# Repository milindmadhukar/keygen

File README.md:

# Keygen

**A wireless split ergonomic keyboard with a custom two-layer PCB designed in KiCad 10.**

Keygen is a one-off build: 66 keys over two column-staggered halves, a 2 × 2 thumb cluster, a rotary
encoder and a 0.96-inch OLED on each half, and per-key RGB lighting. Each half has its own
nRF52840 controller hidden on the PCB underside, and an optional printed wedge tents it 13°. The keyboard reaches the host over Bluetooth or
USB-C, and the halves talk to each other over Bluetooth.

The schematic, placement and most of the routing are generated by the Python scripts in
[`tools/`](tools/), and so are the switch plate and the 3D-printed case.
[`tools/regen.py`](tools/regen.py) keeps every generated file current with its sources. The name and the
silkscreen artwork come from Martin Garrix's track *Keygen* (STMPD RCRDS); see
[Silkscreen artwork](notes/16%20-%20hardware%20reference.md#silkscreen-artwork).
[`tools/check_mechanical.py`](tools/check_mechanical.py) checks the plate, case and component
clearances, including the battery stack at full gasket travel.

**To build one, follow [INSTRUCTIONS.md](INSTRUCTIONS.md).**

## Specifications

| | |
|---|---|
| Layout | Column-staggered QWERTY, six columns per hand plus an extra bottom row |
| Keys | 66 (33 per half): 52 × 1u, 14 × 1.25u |
| Thumb cluster | 2 × 2 block rotated 30° (two 1u over two 1.25u) plus one 1.25u key per hand |
| Encoders | HongYan EC11H with a 20 mm D shaft on each half, fixed to the top frame and plugged into a pin header on the PCB, with a 17 mm aluminium D-shaft knob, in the key matrix. Left: scroll wheel, press for middle click. Right: volume, press to mute |
| Displays | 0.96 in. 128 × 64 SSD1306 OLED per half (I2C), held in the top frame and plugged into the PCB, showing ZMK's status screen |
| Switches | Akko V3 Lavender Purple Pro (tactile, 5-pin) in Kailh hotswap sockets (CPG151101S11) |
| Keycaps | Blank DSA PBT, smoke translucent |
| Lighting | 33 SK6812MINI-E reverse-mount RGB backlights per half, on a 5 V rail from a TPS61023 boost that the firmware switches off with the lighting. An SN74LV1T125 buffer drives their data at 5 V. ZMK's addressable RGB driver; on battery the lighting is optional (a System-layer key), dimmer, and off on a low cell |
| Controller | nRF52840 SuperMini (nice!nano v2 clone, Pro Micro format), one per half, socketed on the underside |
| Connectivity | Host: USB-C (left half) or Bluetooth, 5 profiles. Halves: Bluetooth split |
| Power | KP-355085 LiPo pouch per half (3.5 × 50 × 85 mm, listed 3000 mAh) with a protection board, JST-PH connector, slide switch driving a P-MOSFET battery switch. Each half charges from its own USB-C at about 300 mA |
| PCB | 2 layers, FR-4 1.6 mm, 1 oz copper, HASL, black soldermask with white silkscreen. One half is 160.2 × 126.0 mm |
| Switch plate | Clear polycarbonate 1.5 mm, CNC-routed, with eight gasket tabs per half |
| Case | 3D-printed PETG, gasket-mounted: a bottom shell and a top frame per half, 175.4 × 143.7 × 24.5 mm. The top frame covers the plate round the keycaps and the knob, and holds the OLED and the encoder. Rubber feet, and a steel disc set flush into each floor |
| Tenting | Optional 3D-printed 13° PETG wedge per half, held by four N35 10 × 3 mm magnets to the steel disc, with the feet standing in recesses in its top face |
| Foam | Poron ring switch pads (0.5 mm) on the PCB, EVA plate foam (2 mm) taped under the plate, EVA case foam (5 mm) on the case floor |
| Firmware | [ZMK](https://zmk.dev) `main` (Zephyr 4.1): QWERTY base with Nav, Fn and System layers, ZMK Studio |

## Gallery

The lit pictures are Cycles renders of the [Blender scene](notes/17%20-%20building%20from%20source.md#blender-scene),
which is rebuilt from the board and the case on request; the case layers and the PCB come from KiCad.

<details>
<summary>More renders and animations</summary>

**Both OLEDs booting.** A closeup of both screens playing the firmware boot sequence.

**Per-key lighting.** The SK6812MINI-E LEDs shine up through the switches' clear tops and the smoke
translucent caps. The [logic audit](docs/logic-audit.md) records the current and voltage limits that
still need a powered prototype test before brightness or battery life can be promised.

**All round.**

**From above.** The top frame's deck round the keycaps, the OLED window and the knob.

**From the side.** The back edge of each half, with its USB-C port and power switch.

**Underneath.** The bottom shells, with the counterbored case screws and the reset pinhole.

**Tenting.** Each half on its wedge, and the wedges' top faces: four recesses for the rubber feet, and
four pockets for the magnets under the steel disc.

**Knob and thumb cluster.**

**Status screen.** ZMK's status screen on the left OLED: Bluetooth profile, battery and layer. The
Keygen screens, with their boot animation and lighting menu, are in
[`firmware/README.md`](firmware/README.md#oled-screens).

**Case layers.** Bottom shell, case foam, standoff screws, PCB, switch pads, shims and standoffs,
plate foam, gasket strips under and over the plate tabs, plate and top frame.

**Bare PCB.** Black soldermask with white silkscreen artwork on both sides; see
[Silkscreen artwork](notes/16%20-%20hardware%20reference.md#silkscreen-artwork).

**PCB underside, assembled.** The controllers, power switches, battery connectors and reset buttons
sit on the back.

Renders of the case parts, the plate and the routing are in the [`media` release](https://github.com/milindmadhukar/keygen/releases/tag/media).

</details>

## Documentation

| Document | What it covers |
|---|---|
| [Build guide](INSTRUCTIONS.md) | Parts list, what to order and when, what goes on which side, one section per part with close-ups, flashing, closing the case, troubleshooting |
| [Hardware reference](notes/16%20-%20hardware%20reference.md) | Electronics, PCB rules, plate, case, foam and the silkscreen artwork |
| [Building from source](notes/17%20-%20building%20from%20source.md) | Requirements, the schematic and PCB pipeline, the plate and case, the [Blender scene](notes/17%20-%20building%20from%20source.md#blender-scene), every generated file |
| [Firmware](firmware/README.md) | ZMK configuration: keymap, OLED screens, hardware support, building and flashing |
| [Design notes](notes/index.md) | The Obsidian design notes: layout, controller, PCB, case, final design, datasheet audit |
| [Encoder mount](docs/encoder-mount.md) | The encoder boss, knob clearance, the plate and PCB openings, the cable and a printable test coupon |
| [Build plan](plan/index.html) | Layout drawing, connectivity, parts, pin budget and checklist. Open it in a browser |
| [Printed reference (PDF)](https://github.com/milindmadhukar/keygen/releases/download/build/keygen-reference.pdf) | A4, black and white: each half's key layout with every layer's legends, the case footprint and the back of the board at 1:1, the power parts and each part type close up, the keymap, the key matrix with the controller's pads, and the parts lists |
| [Schematic (PDF)](https://github.com/milindmadhukar/keygen/releases/download/build/keygen-schematic.pdf) | A top sheet with left (refs 1xx) and right (refs 2xx) sub-sheets |
| [KiCad project](pcb/keygen.kicad_pro) | Schematic and PCB, KiCad 10. Both halves are in one board file as two separate outlines |
| [Build files](https://github.com/milindmadhukar/keygen/releases/tag/build) | The PCB and plate Gerbers, case and wedge STLs and STEPs, foam cut files and plate print PDFs, as a release |
| [Ordering notes](fab/ORDER.md) | PCB order-form settings and what to check in the DFM report |
| [Plate ordering notes](case/plate/PLATE.md) | The DXFs for routing the switch plates from polycarbonate sheet, and the Gerbers for an FR-4 plate from a PCB fab |
| [Assembly BOM](fab/BOM.md) | Every part's references per half, with quantities and soldering notes |
| [Parts and sources](plan/bom.html) | Shopping list with Indian and import sources (from [`bom/bom.csv`](bom/bom.csv)) |
| [Shopping checklist](bom/CHECKLIST.md) | What to buy, from which store, with links and prices, to tick off |
| [Datasheets](docs/datasheets/README.md) | Every part's datasheet, with the page each design fact comes from |

## Firmware

Keygen runs [ZMK](https://zmk.dev), one build per half on the nice!nano v2 target, with the left half as
the central. The configuration builds; it has not yet run on the boards. GitHub Actions builds the
UF2s on every push that changes `firmware/`. The keymap, the build and the flashing steps are in
[`firmware/README.md`](firmware/README.md).

## Repository layout

```
keygen/
├── INSTRUCTIONS.md Build guide
├── pcb/            KiCad 10 project: schematic (generated), PCB, plate, project footprints and 3D models
├── tools/          Python scripts that generate, route, check and export the design
├── fab/            Assembly BOMs and ordering notes (the Gerbers are in the build release)
├── case/           Plate ordering notes (the case, wedge, plate and foam files are in the build release)
├── bom/            Bill of materials with sources (bom.csv) and the shopping checklist
├── plan/           Build plan and parts list as HTML
├── docs/           Datasheet index (the PDFs are in the datasheets release)
├── assets/         Keymap pictures and assembly figures (the renders are in the media release)
├── blender/        Blender studio scene with the materials and the lit LEDs; it links the generated parts
├── notes/          Design notes, hardware reference and build pipeline (Obsidian Markdown)
├── firmware/       ZMK configuration: shield, keymap, builds
└── lib/            Git submodules: marbastlib and Keebio-Parts footprint libraries, KeyV2 keycaps
```

## Project status

- [x] Layout and schematic, ERC clean
- [x] PCB placed, routed, DRC clean with schematic parity
- [x] Datasheet audit with no failures
- [x] Manufacturing files and assembly BOM
- [x] Parts sourced and priced
- [ ] Boards ordered and assembled
- [x] ZMK firmware builds
- [ ] ZMK firmware tested on the boards
- [x] Switch plate, gasket-mounted case and tenting wedges designed, fit-checked against the PCB
- [ ] Case and wedges printed

## Credits and licenses

- Footprints from [marbastlib](https://github.com/ebastler/marbastlib) (CERN-OHL-P v2) and
  [Keebio-Parts](https://github.com/keebio/Keebio-Parts.pretty) (MIT), included as git submodules.
- DSA keycap models generated with [KeyV2](https://github.com/rsheldiii/KeyV2) (GPL-3.0), a git submodule.
- MX switch 3D model from [kiswitch](https://github.com/kiswitch/kiswitch) (MIT / CC-BY-SA 4.0); see
  [`pcb/lib/keygen.3dshapes/NOTICE.md`](pcb/lib/keygen.3dshapes/NOTICE.md).
- Datasheets in the [`datasheets` release](https://github.com/milindmadhukar/keygen/releases/tag/datasheets) belong to their manufacturers.

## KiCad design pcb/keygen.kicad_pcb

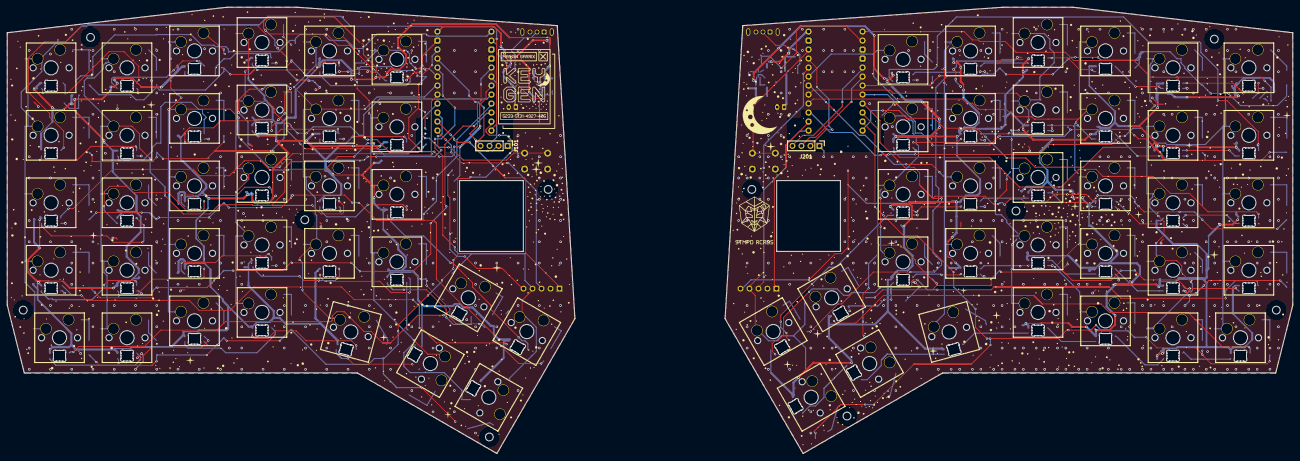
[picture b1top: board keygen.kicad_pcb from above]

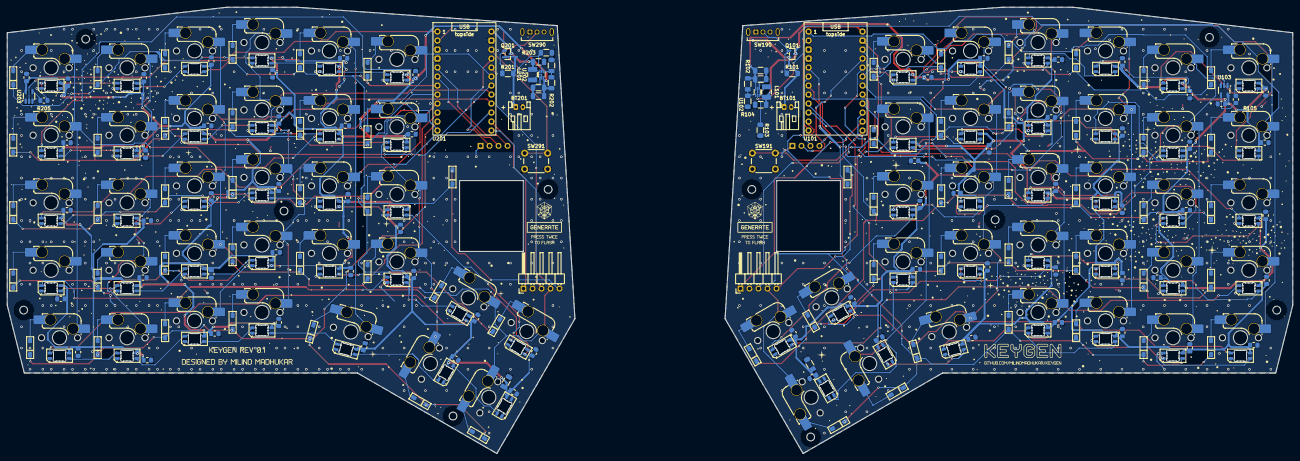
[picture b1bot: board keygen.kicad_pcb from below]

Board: 2 copper layers, 362.9 x 126.0 mm, 318 parts (304 on the bottom side), 190 nets.

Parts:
BT101, BT201: LiPo 3.7V 3000mAh; JST_PH_S2B-PH-K_1x02_P2.00mm_Horizontal
C101, C104, C201, C204: 22uF; C_1206_3216Metric_Pad1.33x1.80mm_HandSolder
C102, C111, C112, C113, C114, C115, C116, C117, C118, C119, C120, C121, C122, C123, C124, C125, C126, C127, C128, C129, C130, C131, C132, C133, C134, C135, C136, C137, C138, C139, C140, C141, C142, C143, C202, C211, C212, C213, C214, C215, C216, C217, C218, C219, C220, C221, C222, C223, C224, C225, C226, C227, C228, C229, C230, C231, C232, C233, C234, C235, C236, C237, C238, C239, C240, C241, C242, C243: 100nF; C_0805_2012Metric_Pad1.18x1.45mm_HandSolder
C103, C105, C203, C205: 10uF; C_1206_3216Metric_Pad1.33x1.80mm_HandSolder
D101, D102, D103, D104, D105, D106, D107, D108, D109, D110, D111, D112, D113, D114, D115, D116, D117, D118, D119, D120, D121, D122, D123, D124, D125, D126, D127, D128, D129, D130, D131, D132, D133, D134, D201, D202, D203, D204, D205, D206, D207, D208, D209, D210, D211, D212, D213, D214, D215, D216, D217, D218, D219, D220, D221, D222, D223, D224, D225, D226, D227, D228, D229, D230, D231, D232, D233, D234: 1N4148W; D_SOD-123_HandSolder
ENC101, ENC201: EC11; EC11_Case_Mount
H101, H102, H103, H104, H105, H201, H202, H203, H204, H205: M2; MountingHole_2.2mm_M2
J101, J201: OLED 0.96in I2C; PinHeader_1x04_P2.54mm_Vertical
J102, J202: Encoder lead, 1x5 right angle; PinHeader_1x05_P2.54mm_Horizontal
L101, L201: 1uH; L_1210_3225Metric_Pad1.42x2.65mm_HandSolder
LED101, LED102, LED103, LED104, LED105, LED106, LED107, LED108, LED109, LED110, LED111, LED112, LED113, LED114, LED115, LED116, LED117, LED118, LED119, LED120, LED121, LED122, LED123, LED124, LED125, LED126, LED127, LED128, LED129, LED130, LED131, LED132, LED133, LED201, LED202, LED203, LED204, LED205, LED206, LED207, LED208, LED209, LED210, LED211, LED212, LED213, LED214, LED215, LED216, LED217, LED218, LED219, LED220, LED221, LED222, LED223, LED224, LED225, LED226, LED227, LED228, LED229, LED230, LED231, LED232, LED233: SK6812MINI-E; LED_SK6812MINI-E_3.2x2.8mm_P1.5mm_ReverseMount
Q101, Q201: AO3401A; SOT-23
R101, R201: 1M; R_1206_3216Metric_Pad1.30x1.75mm_HandSolder
R102, R202: 732k; R_1206_3216Metric_Pad1.30x1.75mm_HandSolder
R103, R104, R203, R204: 100k; R_1206_3216Metric_Pad1.30x1.75mm_HandSolder
R105, R205: 330; R_0805_2012Metric_Pad1.20x1.40mm_HandSolder
SW101: =; SW_MX_HS_CPG151101S11_1.25u
SW102: 1; SW_MX_HS_CPG151101S11_1u
SW103: 2; SW_MX_HS_CPG151101S11_1u
SW104: 3; SW_MX_HS_CPG151101S11_1u
SW105: 4; SW_MX_HS_CPG151101S11_1u
SW106: 5; SW_MX_HS_CPG151101S11_1u
SW108: Tab; SW_MX_HS_CPG151101S11_1.25u
SW109: Q; SW_MX_HS_CPG151101S11_1u
SW110: W; SW_MX_HS_CPG151101S11_1u
SW111: E; SW_MX_HS_CPG151101S11_1u
SW112: R; SW_MX_HS_CPG151101S11_1u
SW113: T; SW_MX_HS_CPG151101S11_1u
SW114: Esc; SW_MX_HS_CPG151101S11_1.25u
SW115: A; SW_MX_HS_CPG151101S11_1u
SW116: S; SW_MX_HS_CPG151101S11_1u
SW117: D; SW_MX_HS_CPG151101S11_1u
SW118: F; SW_MX_HS_CPG151101S11_1u
SW119: G; SW_MX_HS_CPG151101S11_1u
SW120, SW220: Alt; SW_MX_HS_CPG151101S11_1u
SW121, SW221: Shift; SW_MX_HS_CPG151101S11_1.25u
SW122: Z; SW_MX_HS_CPG151101S11_1u
SW123: X; SW_MX_HS_CPG151101S11_1u
SW124: C; SW_MX_HS_CPG151101S11_1u
SW125: V; SW_MX_HS_CPG151101S11_1u
SW126: B; SW_MX_HS_CPG151101S11_1u
SW127, SW227: Ctrl; SW_MX_HS_CPG151101S11_1u
SW128: `; SW_MX_HS_CPG151101S11_1u
SW129: Caps; SW_MX_HS_CPG151101S11_1u
SW130: Left; SW_MX_HS_CPG151101S11_1u
SW131: Right; SW_MX_HS_CPG151101S11_1u
SW132: Super; SW_MX_HS_CPG151101S11_1.25u
SW133: Bksp; SW_MX_HS_CPG151101S11_1.25u
SW134: Del; SW_MX_HS_CPG151101S11_1.25u
SW190, SW290: SK12D07VG5 power; SW_SK12D07VG5
SW191, SW291: Reset; SW_PUSH_6mm_H5mm
SW201: -; SW_MX_HS_CPG151101S11_1.25u
SW202: 0; SW_MX_HS_CPG151101S11_1u
SW203: 9; SW_MX_HS_CPG151101S11_1u
SW204: 8; SW_MX_HS_CPG151101S11_1u
SW205: 7; SW_MX_HS_CPG151101S11_1u
SW206: 6; SW_MX_HS_CPG151101S11_1u
SW208: \; SW_MX_HS_CPG151101S11_1.25u
SW209: P; SW_MX_HS_CPG151101S11_1u
SW210: O; SW_MX_HS_CPG151101S11_1u
SW211: I; SW_MX_HS_CPG151101S11_1u
SW212: U; SW_MX_HS_CPG151101S11_1u
SW213: Y; SW_MX_HS_CPG151101S11_1u
SW214: '; SW_MX_HS_CPG151101S11_1.25u
SW215: ;; SW_MX_HS_CPG151101S11_1u
SW216: L; SW_MX_HS_CPG151101S11_1u
SW217: K; SW_MX_HS_CPG151101S11_1u
SW218: J; SW_MX_HS_CPG151101S11_1u
SW219: H; SW_MX_HS_CPG151101S11_1u
SW222: /; SW_MX_HS_CPG151101S11_1u
SW223: .; SW_MX_HS_CPG151101S11_1u
SW224: ,; SW_MX_HS_CPG151101S11_1u
SW225: M; SW_MX_HS_CPG151101S11_1u
SW226: N; SW_MX_HS_CPG151101S11_1u
SW228: ]; SW_MX_HS_CPG151101S11_1u
SW229: [; SW_MX_HS_CPG151101S11_1u
SW230: Down; SW_MX_HS_CPG151101S11_1u
SW231: Up; SW_MX_HS_CPG151101S11_1u
SW232: Fn; SW_MX_HS_CPG151101S11_1.25u
SW233: Space; SW_MX_HS_CPG151101S11_1.25u
SW234: Enter; SW_MX_HS_CPG151101S11_1.25u
U101, U201: nRF52840 Pro Micro; nice_nano_H_USBup
U102, U202: TPS61023; SOT-563_HandSolder
U103, U203: SN74LV1T125; SOT-23-5_HandSoldering

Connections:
/left/BAT_GATE: Q101.1, R101.1, SW190.2
/left/BAT_RAW: BT101.1, Q101.2, R101.2
/left/COL0: SW101.1, SW108.1, SW114.1, SW121.1, SW128.1, U101.12
/left/COL1: SW102.1, SW109.1, SW115.1, SW122.1, SW129.1, U101.22
/left/COL2: SW103.1, SW110.1, SW116.1, SW123.1, SW130.1, U101.21
/left/COL3: SW104.1, SW111.1, SW117.1, SW124.1, SW131.1, U101.20
/left/COL4: SW105.1, SW112.1, SW118.1, SW125.1, SW132.1, U101.19
/left/COL5: SW106.1, SW113.1, SW119.1, SW126.1, SW133.1, U101.18
/left/COL6: J102.4, SW120.1, SW127.1, SW134.1, U101.17
/left/ENC_A: J102.1, U101.23
/left/ENC_B: J102.3, U101.24
/left/GND: BT101.2, C101.2, C102.2, C103.2, C104.2, C105.2, C111.2, C112.2, C113.2, C114.2, C115.2, C116.2, C117.2, C118.2, C119.2, C120.2, C121.2, C122.2, C123.2, C124.2, C125.2, C126.2, C127.2, C128.2, C129.2, C130.2, C131.2, C132.2, C133.2, C134.2, C135.2, C136.2, C137.2, C138.2, C139.2, C140.2, C141.2, C142.2, C143.2, J101.1, J102.2, LED101.1, LED102.1, LED103.1, LED104.1, LED105.1, LED106.1, LED107.1, LED108.1, LED109.1, LED110.1, LED111.1, LED112.1, LED113.1, LED114.1, LED115.1, LED116.1, LED117.1, LED118.1, LED119.1, LED120.1, LED121.1, LED122.1, LED123.1, LED124.1, LED125.1, LED126.1, LED127.1, LED128.1, LED129.1, LED130.1, LED131.1, LED132.1, LED133.1, R103.2, R104.2, SW190.1, SW191.2, U101.3, U101.4, U101.14, U102.4, U103.1, U103.3
/left/K00: D101.2, SW101.2
/left/K01: D102.2, SW102.2
/left/K02: D103.2, SW103.2
/left/K03: D104.2, SW104.2
/left/K04: D105.2, SW105.2
/left/K05: D106.2, SW106.2
/left/K06: D107.2, J102.5
/left/K10: D108.2, SW108.2
/left/K11: D109.2, SW109.2
/left/K12: D110.2, SW110.2
/left/K13: D111.2, SW111.2
/left/K14: D112.2, SW112.2
/left/K15: D113.2, SW113.2
/left/K20: D114.2, SW114.2
/left/K21: D115.2, SW115.2
/left/K22: D116.2, SW116.2
/left/K23: D117.2, SW117.2
/left/K24: D118.2, SW118.2
/left/K25: D119.2, SW119.2
/left/K26: D120.2, SW120.2
/left/K30: D121.2, SW121.2
/left/K31: D122.2, SW122.2
/left/K32: D123.2, SW123.2
/left/K33: D124.2, SW124.2
/left/K34: D125.2, SW125.2
/left/K35: D126.2, SW126.2
/left/K36: D127.2, SW127.2
/left/K40: D128.2, SW128.2
/left/K41: D129.2, SW129.2
/left/K42: D130.2, SW130.2
/left/K43: D131.2, SW131.2
/left/K44: D132.2, SW132.2
/left/K45: D133.2, SW133.2
/left/K46: D134.2, SW134.2
/left/LED_D0: LED101.2, R105.2
/left/LED_D1: LED101.4, LED102.2
/left/LED_D2: LED102.4, LED103.2
/left/LED_D3: LED103.4, LED104.2
/left/LED_D4: LED104.4, LED105.2
/left/LED_D5: LED105.4, LED106.2
/left/LED_D6: LED106.4, LED107.2
/left/LED_D7: LED107.4, LED108.2
/left/LED_D8: LED108.4, LED109.2
/left/LED_D9: LED109.4, LED110.2
/left/LED_D10: LED110.4, LED111.2
/left/LED_D11: LED111.4, LED112.2
/left/LED_D12: LED112.4, LED113.2
/left/LED_D13: LED113.4, LED114.2
/left/LED_D14: LED114.4, LED115.2
/left/LED_D15: LED115.4, LED116.2
/left/LED_D16: LED116.4, LED117.2
/left/LED_D17: LED117.4, LED118.2
/left/LED_D18: LED118.4, LED119.2
/left/LED_D19: LED119.4, LED120.2
/left/LED_D20: LED120.4, LED121.2
/left/LED_D21: LED121.4, LED122.2
/left/LED_D22: LED122.4, LED123.2
/left/LED_D23: LED123.4, LED124.2
/left/LED_D24: LED124.4, LED125.2
/left/LED_D25: LED125.4, LED126.2
/left/LED_D26: LED126.4, LED127.2
/left/LED_D27: LED127.4, LED128.2
/left/LED_D28: LED128.4, LED129.2
/left/LED_D29: LED129.4, LED130.2
/left/LED_D30: LED130.4, LED131.2
/left/LED_D31: LED131.4, LED132.2
/left/LED_D32: LED132.4, LED133.2
/left/LED_DIN: U101.1, U103.2
/left/LED_DY: R105.1, U103.4
/left/LED_EN: R103.1, U101.2, U102.2
/left/LED_FB: R102.2, R104.1, U102.1
/left/LED_SW: L101.2, U102.5
/left/LED_VDD: C101.1, C102.1, C104.1, C105.1, C111.1, C112.1, C113.1, C114.1, C115.1, C116.1, C117.1, C118.1, C119.1, C120.1, C121.1, C122.1, C123.1, C124.1, C125.1, C126.1, C127.1, C128.1, C129.1, C130.1, C131.1, C132.1, C133.1, C134.1, C135.1, C136.1, C137.1, C138.1, C139.1, C140.1, C141.1, C142.1, C143.1, LED101.3, LED102.3, LED103.3, LED104.3, LED105.3, LED106.3, LED107.3, LED108.3, LED109.3, LED110.3, LED111.3, LED112.3, LED113.3, LED114.3, LED115.3, LED116.3, LED117.3, LED118.3, LED119.3, LED120.3, LED121.3, LED122.3, LED123.3, LED124.3, LED125.3, LED126.3, LED127.3, LED128.3, LED129.3, LED130.3, LED131.3, LED132.3, LED133.3, R102.1, U102.6, U103.5
/left/OLED_SCL: J101.3, U101.6
/left/OLED_SDA: J101.4, U101.5
/left/ROW0: D101.1, D102.1, D103.1, D104.1, D105.1, D106.1, D107.1, U101.7
/left/ROW1: D108.1, D109.1, D110.1, D111.1, D112.1, D113.1, U101.8
/left/ROW2: D114.1, D115.1, D116.1, D117.1, D118.1, D119.1, D120.1, U101.9
/left/ROW3: D121.1, D122.1, D123.1, D124.1, D125.1, D126.1, D127.1, U101.10
/left/ROW4: D128.1, D129.1, D130.1, D131.1, D132.1, D133.1, D134.1, U101.11
/left/RST: SW191.1, U101.15
/left/VBAT: C103.1, L101.1, Q101.3, U101.13, U102.3
/left/VCC: J101.2, U101.16
/right/BAT_GATE: Q201.1, R201.1, SW290.2
/right/BAT_RAW: BT201.1, Q201.2, R201.2
/right/COL0: SW201.1, SW208.1, SW214.1, SW221.1, SW228.1, U201.12
/right/COL1: SW202.1, SW209.1, SW215.1, SW222.1, SW229.1, U201.22
/right/COL2: SW203.1, SW210.1, SW216.1, SW223.1, SW230.1, U201.21
/right/COL3: SW204.1, SW211.1, SW217.1, SW224.1, SW231.1, U201.20
/right/COL4: SW205.1, SW212.1, SW218.1, SW225.1, SW232.1, U201.19
/right/COL5: SW206.1, SW213.1, SW219.1, SW226.1, SW233.1, U201.18
/right/COL6: J202.4, SW220.1, SW227.1, SW234.1, U201.17
/right/ENC_A: J202.1, U201.23
/right/ENC_B: J202.3, U201.24
/right/GND: BT201.2, C201.2, C202.2, C203.2, C204.2, C205.2, C211.2, C212.2, C213.2, C214.2, C215.2, C216.2, C217.2, C218.2, C219.2, C220.2, C221.2, C222.2, C223.2, C224.2, C225.2, C226.2, C227.2, C228.2, C229.2, C230.2, C231.2, C232.2, C233.2, C234.2, C235.2, C236.2, C237.2, C238.2, C239.2, C240.2, C241.2, C242.2, C243.2, J201.1, J202.2, LED201.1, LED202.1, LED203.1, LED204.1, LED205.1, LED206.1, LED207.1, LED208.1, LED209.1, LED210.1, LED211.1, LED212.1, LED213.1, LED214.1, LED215.1, LED216.1, LED217.1, LED218.1, LED219.1, LED220.1, LED221.1, LED222.1, LED223.1, LED224.1, LED225.1, LED226.1, LED227.1, LED228.1, LED229.1, LED230.1, LED231.1, LED232.1, LED233.1, R203.2, R204.2, SW290.1, SW291.2, U201.3, U201.4, U201.14, U202.4, U203.1, U203.3
/right/K00: D201.2, SW201.2
/right/K01: D202.2, SW202.2
/right/K02: D203.2, SW203.2
/right/K03: D204.2, SW204.2
/right/K04: D205.2, SW205.2
/right/K05: D206.2, SW206.2
/right/K06: D207.2, J202.5
/right/K10: D208.2, SW208.2
/right/K11: D209.2, SW209.2
/right/K12: D210.2, SW210.2
/right/K13: D211.2, SW211.2
/right/K14: D212.2, SW212.2
/right/K15: D213.2, SW213.2
/right/K20: D214.2, SW214.2
/right/K21: D215.2, SW215.2
/right/K22: D216.2, SW216.2
/right/K23: D217.2, SW217.2
/right/K24: D218.2, SW218.2
/right/K25: D219.2, SW219.2
/right/K26: D220.2, SW220.2
/right/K30: D221.2, SW221.2
/right/K31: D222.2, SW222.2
/right/K32: D223.2, SW223.2
/right/K33: D224.2, SW224.2
/right/K34: D225.2, SW225.2
/right/K35: D226.2, SW226.2
/right/K36: D227.2, SW227.2
/right/K40: D228.2, SW228.2
/right/K41: D229.2, SW229.2
/right/K42: D230.2, SW230.2
/right/K43: D231.2, SW231.2
/right/K44: D232.2, SW232.2
/right/K45: D233.2, SW233.2
/right/K46: D234.2, SW234.2
/right/LED_D0: LED201.2, R205.2
/right/LED_D1: LED201.4, LED202.2
/right/LED_D2: LED202.4, LED203.2
/right/LED_D3: LED203.4, LED204.2
/right/LED_D4: LED204.4, LED205.2
/right/LED_D5: LED205.4, LED206.2
/right/LED_D6: LED206.4, LED207.2
/right/LED_D7: LED207.4, LED208.2
/right/LED_D8: LED208.4, LED209.2
/right/LED_D9: LED209.4, LED210.2
/right/LED_D10: LED210.4, LED211.2
/right/LED_D11: LED211.4, LED212.2
/right/LED_D12: LED212.4, LED213.2
/right/LED_D13: LED213.4, LED214.2
/right/LED_D14: LED214.4, LED215.2
/right/LED_D15: LED215.4, LED216.2
/right/LED_D16: LED216.4, LED217.2
/right/LED_D17: LED217.4, LED218.2
/right/LED_D18: LED218.4, LED219.2
/right/LED_D19: LED219.4, LED220.2
/right/LED_D20: LED220.4, LED221.2
/right/LED_D21: LED221.4, LED222.2
/right/LED_D22: LED222.4, LED223.2
/right/LED_D23: LED223.4, LED224.2
/right/LED_D24: LED224.4, LED225.2
/right/LED_D25: LED225.4, LED226.2
/right/LED_D26: LED226.4, LED227.2
/right/LED_D27: LED227.4, LED228.2
/right/LED_D28: LED228.4, LED229.2
/right/LED_D29: LED229.4, LED230.2
/right/LED_D30: LED230.4, LED231.2
/right/LED_D31: LED231.4, LED232.2
/right/LED_D32: LED232.4, LED233.2
/right/LED_DIN: U201.1, U203.2
/right/LED_DY: R205.1, U203.4
/right/LED_EN: R203.1, U201.2, U202.2
/right/LED_FB: R202.2, R204.1, U202.1
/right/LED_SW: L201.2, U202.5
/right/LED_VDD: C201.1, C202.1, C204.1, C205.1, C211.1, C212.1, C213.1, C214.1, C215.1, C216.1, C217.1, C218.1, C219.1, C220.1, C221.1, C222.1, C223.1, C224.1, C225.1, C226.1, C227.1, C228.1, C229.1, C230.1, C231.1, C232.1, C233.1, C234.1, C235.1, C236.1, C237.1, C238.1, C239.1, C240.1, C241.1, C242.1, C243.1, LED201.3, LED202.3, LED203.3, LED204.3, LED205.3, LED206.3, LED207.3, LED208.3, LED209.3, LED210.3, LED211.3, LED212.3, LED213.3, LED214.3, LED215.3, LED216.3, LED217.3, LED218.3, LED219.3, LED220.3, LED221.3, LED222.3, LED223.3, LED224.3, LED225.3, LED226.3, LED227.3, LED228.3, LED229.3, LED230.3, LED231.3, LED232.3, LED233.3, R202.1, U202.6, U203.5
/right/OLED_SCL: J201.3, U201.6
/right/OLED_SDA: J201.4, U201.5
/right/ROW0: D201.1, D202.1, D203.1, D204.1, D205.1, D206.1, D207.1, U201.7
/right/ROW1: D208.1, D209.1, D210.1, D211.1, D212.1, D213.1, U201.8
/right/ROW2: D214.1, D215.1, D216.1, D217.1, D218.1, D219.1, D220.1, U201.9
/right/ROW3: D221.1, D222.1, D223.1, D224.1, D225.1, D226.1, D227.1, U201.10
/right/ROW4: D228.1, D229.1, D230.1, D231.1, D232.1, D233.1, D234.1, U201.11
/right/RST: SW291.1, U201.15
/right/VBAT: C203.1, L201.1, Q201.3, U201.13, U202.3
/right/VCC: J201.2, U201.16

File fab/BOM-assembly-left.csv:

Item Number,Designator,Unit Quantity,Description,Manufacturer Part Number,Footprint,Value,Assembly Instructions
1,BT101,1,JST-PH 2-pin battery connector,S2B-PH-K-S(LF)(SN) (JST),Connector_JST:JST_PH_S2B-PH-K_1x02_P2.00mm_Horizontal,JST-PH 2-pin,"THT side-entry, BOTTOM side. Opening toward the battery pocket."
2,"C101,C104",2,22 µF capacitor (1206),"CS3216X7R226K160NRI (Samwha, 22 µF 16 V X7R 1206)",Capacitor_SMD:C_1206_3216Metric_Pad1.33x1.80mm_HandSolder,22uF,BOTTOM side.
3,C102,1,100 nF capacitor (0805),100 nF 50 V X7R 0805 (any),Capacitor_SMD:C_0805_2012Metric_Pad1.18x1.45mm_HandSolder,100nF,BOTTOM side.
4,"C103,C105",2,10 µF capacitor (1206),"CL31A106KBHNNNE (Samsung, 10 µF 50 V X5R 1206)",Capacitor_SMD:C_1206_3216Metric_Pad1.33x1.80mm_HandSolder,10uF,BOTTOM side.
5,"C111,C112,C113,C114,C115,C116,C117,C118,C119,C120,C121,C122,C123,C124,C125,C126,C127,C128,C129,C130,C131,C132,C133,C134,C135,C136,C137,C138,C139,C140,C141,C142,C143",33,"100 nF capacitor (0805), optional",,Capacitor_SMD:C_0805_2012Metric_Pad1.18x1.45mm_HandSolder,100nF,DO NOT FIT: optional footprints.
6,"D101,D102,D103,D104,D105,D106,D107,D108,D109,D110,D111,D112,D113,D114,D115,D116,D117,D118,D119,D120,D121,D122,D123,D124,D125,D126,D127,D128,D129,D130,D131,D132,D133,D134",34,1N4148W diode,"1N4148W-7-F (Diodes Incorporated, SOD-123)",keygen:D_SOD-123_HandSolder,1N4148W,"SMD, BOTTOM side. Polarity: band (cathode) to pad 1."
7,ENC101,1,EC11 rotary encoder,"EC11 with push switch, 20 mm D shaft (Hongyan EC11)",keygen:EC11_Case_Mount,EC11,DO NOT FIT: not on the PCB; customer mounts it in the case and plugs it into the 5-pin header.
8,J101,1,OLED 0.96in I2C,,Connector_PinHeader_2.54mm:PinHeader_1x04_P2.54mm_Vertical,OLED 0.96in I2C,TOP side.
9,J102,1,1x5 right-angle pin header,"1x5 right-angle male pin header, 2.54 mm (any)",Connector_PinHeader_2.54mm:PinHeader_1x05_P2.54mm_Horizontal,"Encoder lead, 1x5 right angle","THT right angle, BOTTOM side, pins lying flat and pointing away from the thumb keys."
10,L101,1,1 µH inductor (1210),TMS322512ALM-1R0MTAA (TDK),Inductor_SMD:L_1210_3225Metric_Pad1.42x2.65mm_HandSolder,1uH,BOTTOM side.
11,"LED101,LED102,LED103,LED104,LED105,LED106,LED107,LED108,LED109,LED110,LED111,LED112,LED113,LED114,LED115,LED116,LED117,LED118,LED119,LED120,LED121,LED122,LED123,LED124,LED125,LED126,LED127,LED128,LED129,LED130,LED131,LED132,LED133",33,SK6812MINI-E LED,"SK6812MINI-E (OPSCO, LCSC C5149201)",LED_SMD:LED_SK6812MINI-E_3.2x2.8mm_P1.5mm_ReverseMount,SK6812MINI-E,"Reverse-mount LED, BOTTOM side, body through the PCB cut-out. Match the corner mark to the footprint's pin-1 mark."
12,Q101,1,AO3401A P-MOSFET (SOT-23),"AO3401A (Alpha & Omega, SOT-23)",Package_TO_SOT_SMD:SOT-23,AO3401A,BOTTOM side.
13,R101,1,1 MΩ resistor (1206),"1206W4F1004T5E (UNI-ROYAL, 1 MΩ 1% 1206)",Resistor_SMD:R_1206_3216Metric_Pad1.30x1.75mm_HandSolder,1M,BOTTOM side.
14,R102,1,"732 kΩ resistor, 1 % (1206)",RC1206FR-07732KL (Yageo),Resistor_SMD:R_1206_3216Metric_Pad1.30x1.75mm_HandSolder,732k,BOTTOM side.
15,"R103,R104",2,"100 kΩ resistor, 1 % (1206)",RC1206FR-13100KL (Yageo),Resistor_SMD:R_1206_3216Metric_Pad1.30x1.75mm_HandSolder,100k,BOTTOM side.
16,R105,1,330 Ω resistor (0805),RC0805FR-07330RL (Yageo),Resistor_SMD:R_0805_2012Metric_Pad1.20x1.40mm_HandSolder,330,BOTTOM side.
17,"SW101,SW108,SW114,SW121,SW132,SW133,SW134",7,Kailh MX hotswap socket for a 1.25u key,CPG151101S11 (Kailh),keygen:SW_MX_HS_CPG151101S11_1.25u,Kailh hotswap socket,"Kailh CPG151101S11 hotswap socket, BOTTOM side. Do NOT fit switches (customer installs)."
18,"SW102,SW103,SW104,SW105,SW106,SW109,SW110,SW111,SW112,SW113,SW115,SW116,SW117,SW118,SW119,SW120,SW122,SW123,SW124,SW125,SW126,SW127,SW128,SW129,SW130,SW131",26,Kailh MX hotswap socket for a 1u key,CPG151101S11 (Kailh),keygen:SW_MX_HS_CPG151101S11_1u,Kailh hotswap socket,"Kailh CPG151101S11 hotswap socket, BOTTOM side. Do NOT fit switches (customer installs)."
19,SW190,1,SK12D07VG5 power slide switch,"SK12D07VG5 (Shou Han, LCSC C431548)",keygen:SW_SK12D07VG5,SK12D07VG5 power,BOTTOM side.
20,SW191,1,6 mm reset button,"6x6x5 mm THT tactile switch (e.g. TS-1102S-B-B, any 6x6x5)",Button_Switch_THT:SW_PUSH_6mm_H5mm,Reset,BOTTOM side.
21,U101,1,nRF52840 SuperMini (nice!nano v2 clone),Customer supplied: nRF52840 SuperMini (nice!nano v2 clone),keygen:nice_nano_H_USBup,nRF52840 Pro Micro,DO NOT FIT: customer solders sockets + controller (BOTTOM side).
22,U102,1,TPS61023 boost converter (SOT-563),TPS61023DRLR (Texas Instruments),keygen:SOT-563_HandSolder,TPS61023,BOTTOM side.
23,U103,1,SN74LV1T125 buffer (SOT-23-5),SN74LV1T125DBVR (Texas Instruments),Package_TO_SOT_SMD:SOT-23-5_HandSoldering,SN74LV1T125,BOTTOM side.

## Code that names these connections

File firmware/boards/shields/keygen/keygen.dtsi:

/*
 * Keygen: both halves. Pins follow tools/gen_schematic.py (MCU_PINS, MCU_NETS); the controller
 * is a nice!nano v2, so pins are written as nRF52840 GPIOs rather than Pro Micro numbers.
 */

#include "keygen-layouts.dtsi"

/ {
    chosen {
        zmk,kscan = &kscan0;
        zmk,physical-layout = &keygen_layout;
    };

    /* 5 x 7 per half, COL2ROW: switch to the column, diode cathode to the row */
    kscan0: kscan {
        compatible = "zmk,kscan-gpio-matrix";
        wakeup-source;
        diode-direction = "col2row";

        row-gpios
            = <&gpio0 22 (GPIO_ACTIVE_HIGH | GPIO_PULL_DOWN)>   /* ROW0, pad 7  */
            , <&gpio0 24 (GPIO_ACTIVE_HIGH | GPIO_PULL_DOWN)>   /* ROW1, pad 8  */
            , <&gpio1 0  (GPIO_ACTIVE_HIGH | GPIO_PULL_DOWN)>   /* ROW2, pad 9  */
            , <&gpio0 11 (GPIO_ACTIVE_HIGH | GPIO_PULL_DOWN)>   /* ROW3, pad 10 */
            , <&gpio1 4  (GPIO_ACTIVE_HIGH | GPIO_PULL_DOWN)>   /* ROW4, pad 11 */
            ;
        col-gpios                                               /* COL0 is the outer edge */
            = <&gpio1 6  GPIO_ACTIVE_HIGH>                      /* COL0, pad 12 */
            , <&gpio1 11 GPIO_ACTIVE_HIGH>                      /* COL1, pad 22 */
            , <&gpio1 13 GPIO_ACTIVE_HIGH>                      /* COL2, pad 21 */
            , <&gpio1 15 GPIO_ACTIVE_HIGH>                      /* COL3, pad 20 */
            , <&gpio0 2  GPIO_ACTIVE_HIGH>                      /* COL4, pad 19 */
            , <&gpio0 29 GPIO_ACTIVE_HIGH>                      /* COL5, pad 18 */
            , <&gpio0 31 GPIO_ACTIVE_HIGH>                      /* COL6, pad 17 */
            ;
    };

    /* An EC11 on each half, on the same pins; each push switch is in its half's matrix at
     * row 0 / column 6. Each half's overlay enables its own. */
    left_encoder: encoder_left {
        compatible = "alps,ec11";
        a-gpios = <&gpio0 10 (GPIO_ACTIVE_HIGH | GPIO_PULL_UP)>;   /* ENC_A, pad 23 (NFC2) */
        b-gpios = <&gpio0 9  (GPIO_ACTIVE_HIGH | GPIO_PULL_UP)>;   /* ENC_B, pad 24 (NFC1) */
        steps = <80>;
        status = "disabled";
    };

    right_encoder: encoder_right {
        compatible = "alps,ec11";
        a-gpios = <&gpio0 10 (GPIO_ACTIVE_HIGH | GPIO_PULL_UP)>;   /* ENC_A, pad 23 (NFC2) */
        b-gpios = <&gpio0 9  (GPIO_ACTIVE_HIGH | GPIO_PULL_UP)>;   /* ENC_B, pad 24 (NFC1) */
        steps = <80>;
        status = "disabled";
    };

    sensors: sensors {
        compatible = "zmk,keymap-sensors";
        sensors = <&left_encoder &right_encoder>;
        triggers-per-rotation = <20>;
    };
};

/* Both encoder lines are on the NFC pins */
&uicr {
    nfct-pins-as-gpios;
};

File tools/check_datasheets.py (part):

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       f"{side}: B+ is fed only by the battery MOSFET's drain (Q{d}01 pin 3) and feeds the controller and the "
       f"boost's VIN, inductor and input capacitor",
       f"{side}: VBAT = {sorted(nodes(side, 'VBAT'))}")
    ok(nodes(side, "LED_SW") == {(U2, "5"), (L1, "2")}, A, f"{side}: the inductor joins VIN to the boost's SW pin",
       f"{side}: LED_SW = {sorted(nodes(side, 'LED_SW'))}")
    feeders = {(r_, p_) for r_, p_ in nodes(side, "LED_VDD") if not re.match(r"(LED|C)\d+$", r_)}
    ok(feeders == {(U2, "6"), (R2, "1"), (f"U{d}03", "5")}, A,
       f"{side}: LED_VDD is driven only by the boost's VOUT (U{d}02 pin 6); it feeds the LEDs, the buffer and the divider",
       f"{side}: LED_VDD non-capacitor nodes {sorted(feeders)}")
    ok(nodes(side, "LED_FB") == {(U2, "1"), (R2, "2"), (R4, "1")} and pad_net(R4, "2") == "GND", A,
       f"{side}: feedback divider R{d}02 (VOUT to FB) and R{d}04 (FB to GND)")
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    ok(rows == {f"ROW{i}" for i in range(5)}, A, f"{side}: 5 rows and 7 columns all reach the controller")
    e = pads(f"J{d}02")
    ok(net(e["2"]) == "GND", A, f"{side}: encoder lead pin 2 (EC11 common C, the middle pin) on GND")
    ok((net(e["1"]), net(e["3"])) == ("ENC_A", "ENC_B"), A, f"{side}: encoder lead pins 1 and 3 on ENC_A/ENC_B (inputs with internal pull-ups)")
    ok(re.match(r"COL\d$", net(e["4"])) and re.match(r"K\d+$", net(e["5"])), A, f"{side}: encoder lead pins 4 and 5 are the push switch, COL and diode")

# --------------------------------------------------------------------------------------
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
